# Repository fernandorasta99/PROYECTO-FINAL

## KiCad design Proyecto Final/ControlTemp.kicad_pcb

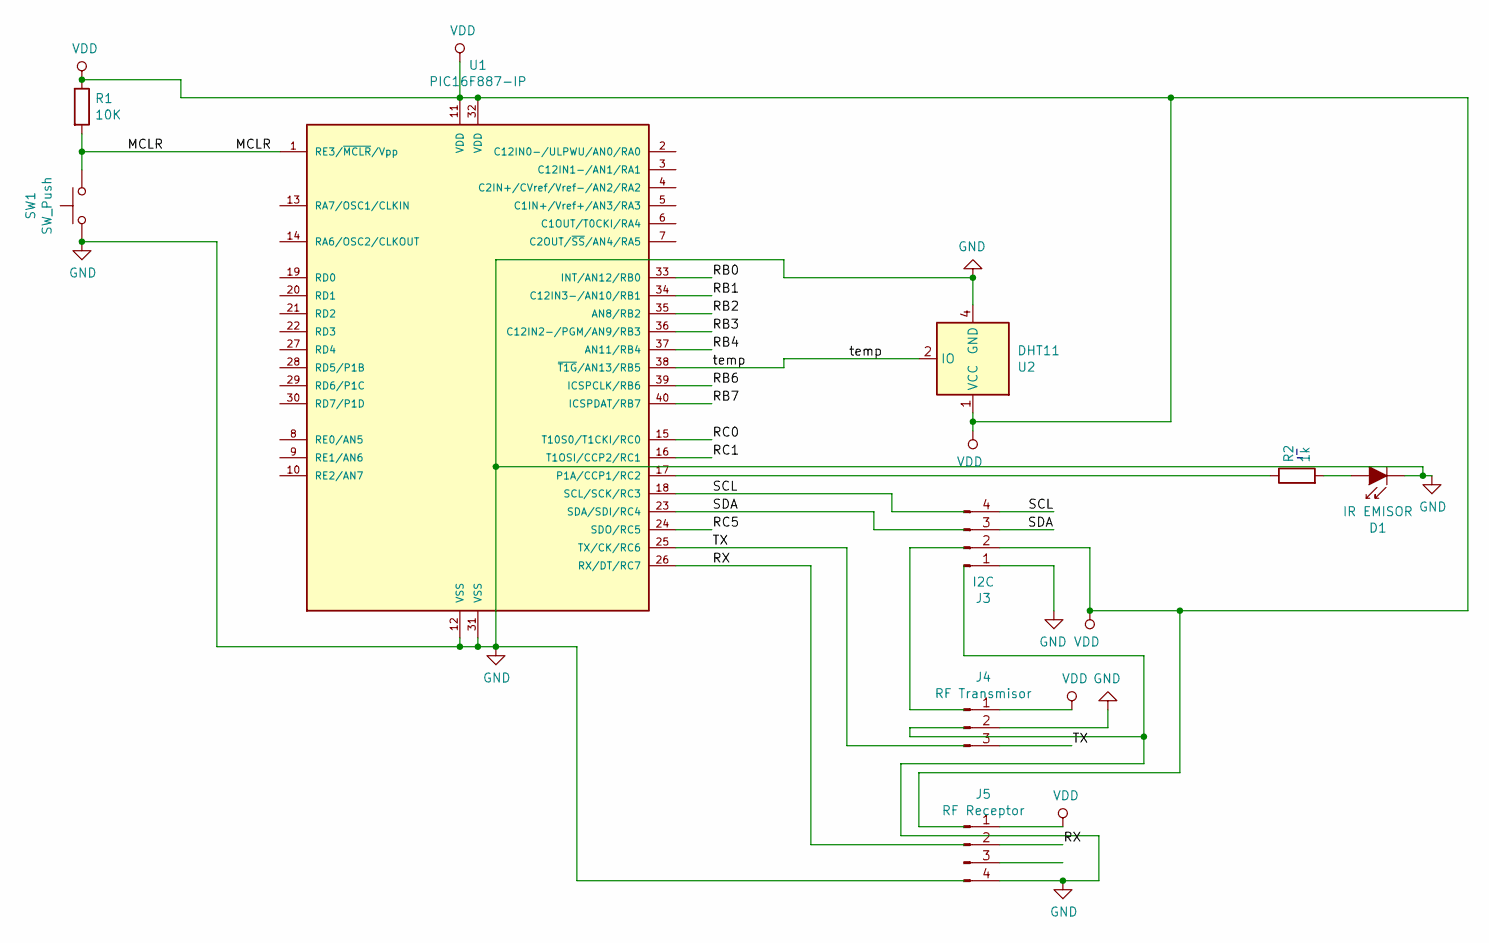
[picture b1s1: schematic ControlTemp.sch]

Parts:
D1: IR EMISOR; LED_D3.0mm_IRBlack
J3: I2C; PinSocket_1x04_P2.54mm_Vertical
J4: RF Transmisor; PinSocket_1x03_P2.54mm_Vertical
J5: RF Receptor; PinSocket_1x04_P2.54mm_Vertical
R1: 10K; R_0805_2012Metric
R2: 1k; R_0805_2012Metric
SW1: SW_Push; SW_PUSH_6mm
U1: PIC16F887-IP; DIP-40_W15.24mm_Socket
U2: DHT11; Aosong_DHT11_5.5x12.0_P2.54mm

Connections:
/MCLR: R1.2, SW1.2, U1.1 (RE3/~MCLR~/Vpp)
/RB0: U1.33 (INT/AN12/RB0)
/RB1: U1.34 (C12IN3-/AN10/RB1)
/RB2: U1.35 (AN8/RB2)
/RB3: U1.36 (C12IN2-/PGM/AN9/RB3)
/RB4: U1.37 (AN11/RB4)
/RB6: U1.39 (ICSPCLK/RB6)
/RB7: U1.40 (ICSPDAT/RB7)
/RC0: U1.15 (T10S0/T1CKI/RC0)
/RC1: U1.16 (T1OSI/CCP2/RC1)
/RC5: U1.24 (SDO/RC5)
/RX: J5.2, U1.26 (RX/DT/RC7)
/SCL: J3.4, U1.18 (SCL/SCK/RC3)
/SDA: J3.3, U1.23 (SDA/SDI/RC4)
/TX: J4.3, U1.25 (TX/CK/RC6)
/temp: U1.38 (~T1G~/AN13/RB5), U2.2 (IO)
GND: D1.1 (K), J3.1, J4.2, J5.4, SW1.1, U1.12 (VSS), U1.31 (VSS), U2.4 (GND)
unnamed: D1.2 (A), R2.2
unnamed: R2.1, U1.17 (P1A/CCP1/RC2)
VDD: J3.2, J4.1, J5.1, R1.1, U1.11 (VDD), U1.32 (VDD), U2.1 (VCC)

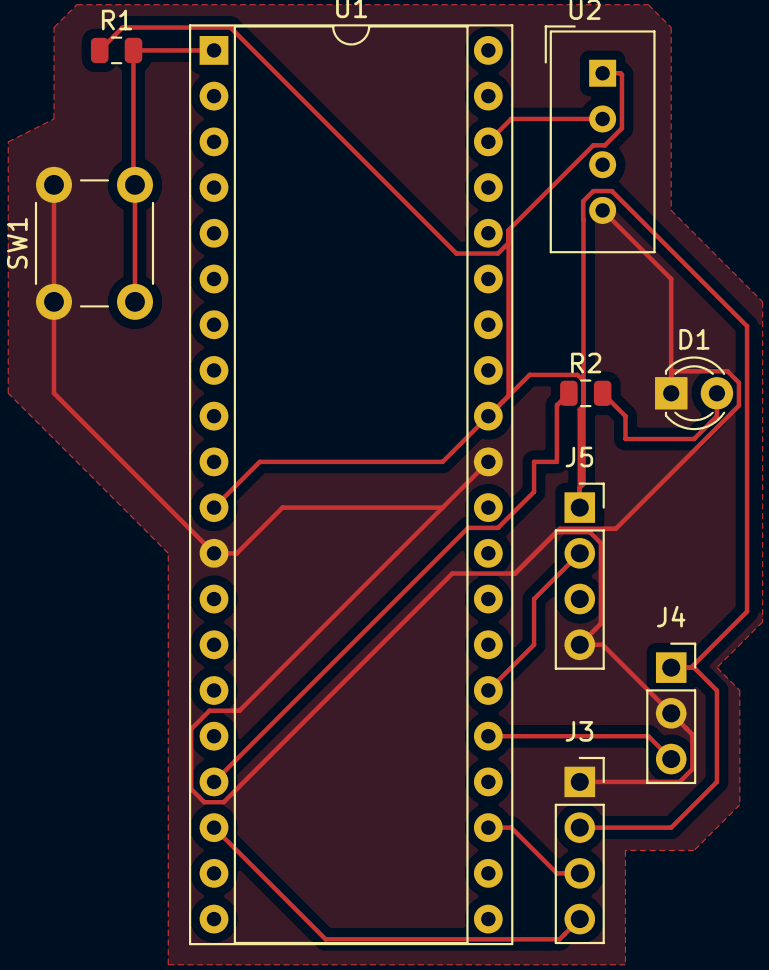
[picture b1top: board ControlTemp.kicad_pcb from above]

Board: 2 copper layers, 9 parts (0 on the bottom side), 10 nets.
